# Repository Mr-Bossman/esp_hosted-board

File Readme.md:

# Test board for esp-hosted-ng

## Esp-hosted-ng is a SDIO/SPI WIFI/BT module for hosts runing Linux

To test ESP-Hosted-ng I designed this board to plug into and SD-card slot for easy testing.

The mothod I used before has some major signal integrity loss due to the jumper wires I used.

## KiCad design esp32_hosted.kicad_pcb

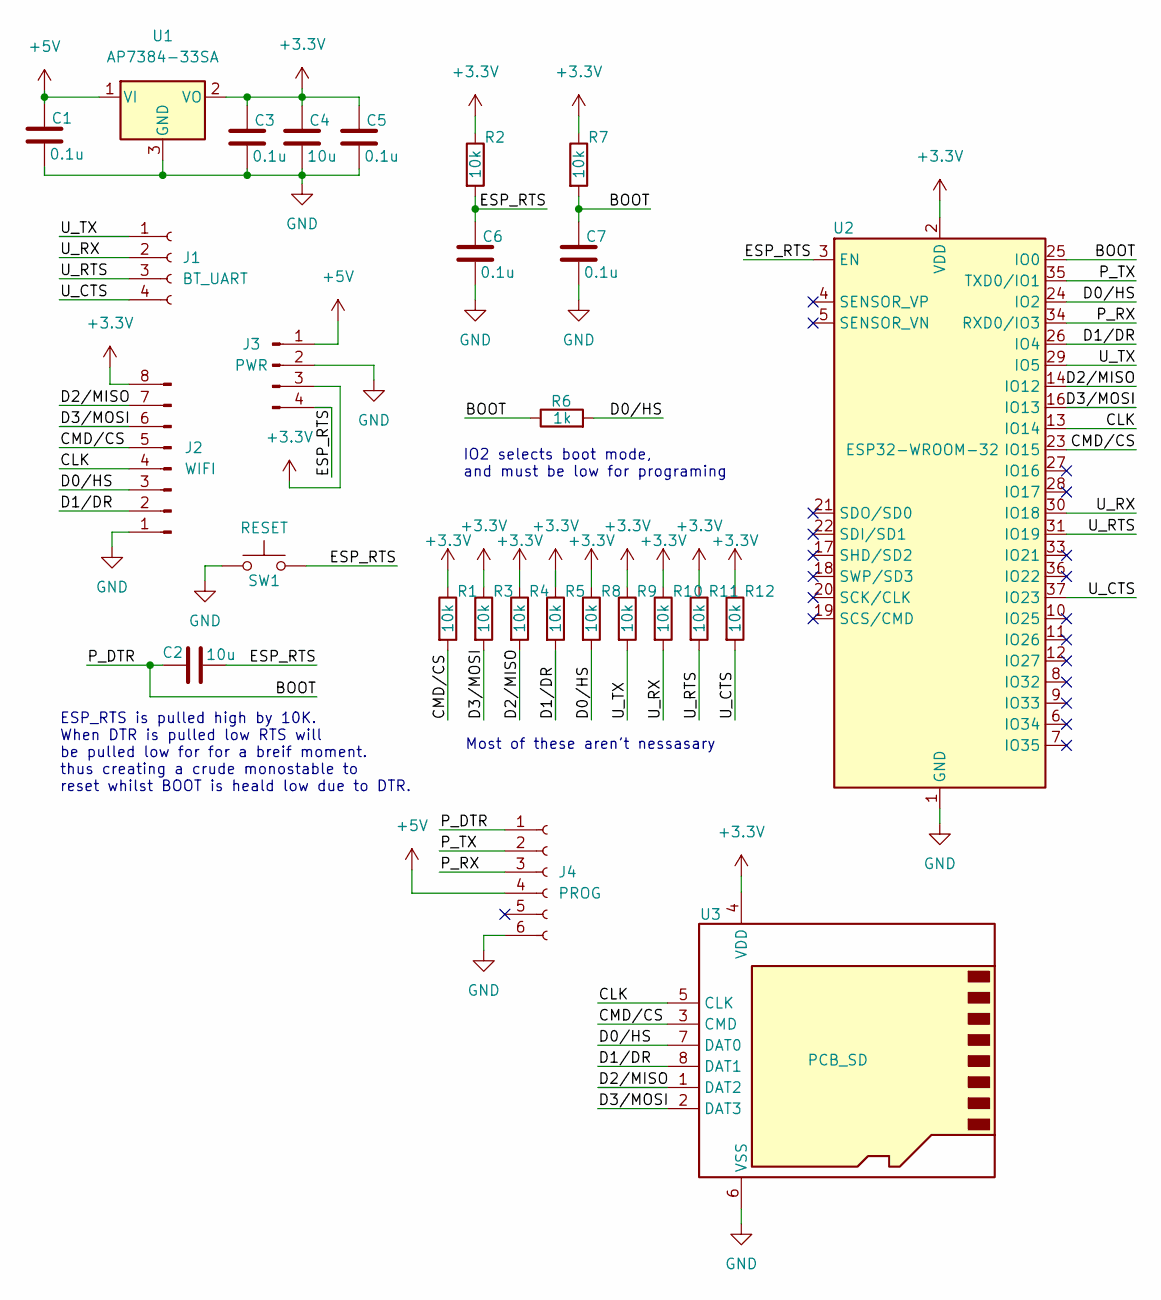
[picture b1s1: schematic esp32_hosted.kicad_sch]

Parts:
C1, C3, C5, C6, C7: 0.1u; C_0603_1608Metric_Pad1.08x0.95mm_HandSolder
C2, C4: 10u; C_0603_1608Metric_Pad1.08x0.95mm_HandSolder
J1: BT_UART; PinSocket_1x04_P2.54mm_Vertical
J2: WIFI; PinSocket_1x08_P2.54mm_Vertical
J3: PWR; PinSocket_1x04_P2.54mm_Vertical
J4: PROG; PinHeader_1x06_P2.54mm_Vertical
R1, R2, R3, R4, R5, R7, R8, R9, R10, R11, R12: 10k; C_0603_1608Metric_Pad1.08x0.95mm_HandSolder
R6: 1k; C_0603_1608Metric_Pad1.08x0.95mm_HandSolder
SW1: RESET; SW_PUSH_6mm
U1: AP7384-33SA; SOT-23
U2: ESP32-WROOM-32
U3: PCB_SD; PCB-SD

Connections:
+3.3V: C3.1, C4.1, C5.1, J2.8, J3.3, R1.1, R2.1, R3.1, R4.1, R5.1, R7.1, R8.1, R9.1, R10.1, R11.1, R12.1, U1.2 (VO), U2.2 (VDD), U3.4 (VDD)
+5V: C1.1, J3.1, J4.4, U1.1 (VI)
/BOOT: C2.1, C7.1, J4.1, R6.1, R7.2, U2.25 (IO0)
/CLK: J2.4, U2.13 (IO14), U3.5 (CLK)
/CMD/CS: J2.5, R1.2, U2.23 (IO15), U3.3 (CMD)
/D0/HS: J2.3, R6.2, R8.2, U2.24 (IO2), U3.7 (DAT0)
/D1/DR: J2.2, R5.2, U2.26 (IO4), U3.8 (DAT1)
/D2/MISO: J2.7, R4.2, U2.14 (IO12), U3.1 (DAT2)
/D3/MOSI: J2.6, R3.2, U2.16 (IO13), U3.2 (DAT3)
/ESP_RTS: C2.2, C6.1, J3.4, R2.2, SW1.2, U2.3 (EN)
/P_RX: J4.3, U2.34 (RXD0/IO3)
/P_TX: J4.2, U2.35 (TXD0/IO1)
/U_CTS: J1.4, R12.2, U2.37 (IO23)
/U_RTS: J1.3, R11.2, U2.31 (IO19)
/U_RX: J1.2, R10.2, U2.30 (IO18)
/U_TX: J1.1, R9.2, U2.29 (IO5)
GND: C1.2, C3.2, C4.2, C5.2, C6.2, C7.2, J2.1, J3.2, J4.6, SW1.1, U1.3 (GND), U2.1 (GND), U2.15 (GND), U2.38 (GND), U2.39 (GND), U3.6 (VSS)

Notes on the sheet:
IO2 selects boot mode, and must be low for programing
ESP_RTS is pulled high by 10K. When DTR is pulled low RTS will be pulled low for for a breif moment. thus creating a crude monostable to reset whilst BOOT is heald low due to DTR.
Most of these aren't nessasary

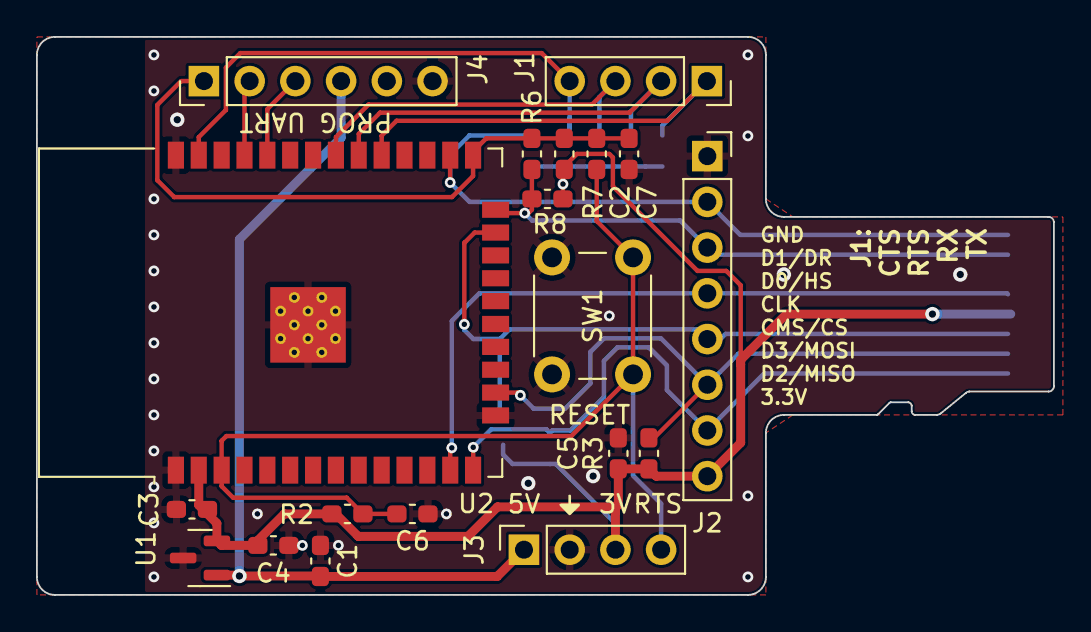
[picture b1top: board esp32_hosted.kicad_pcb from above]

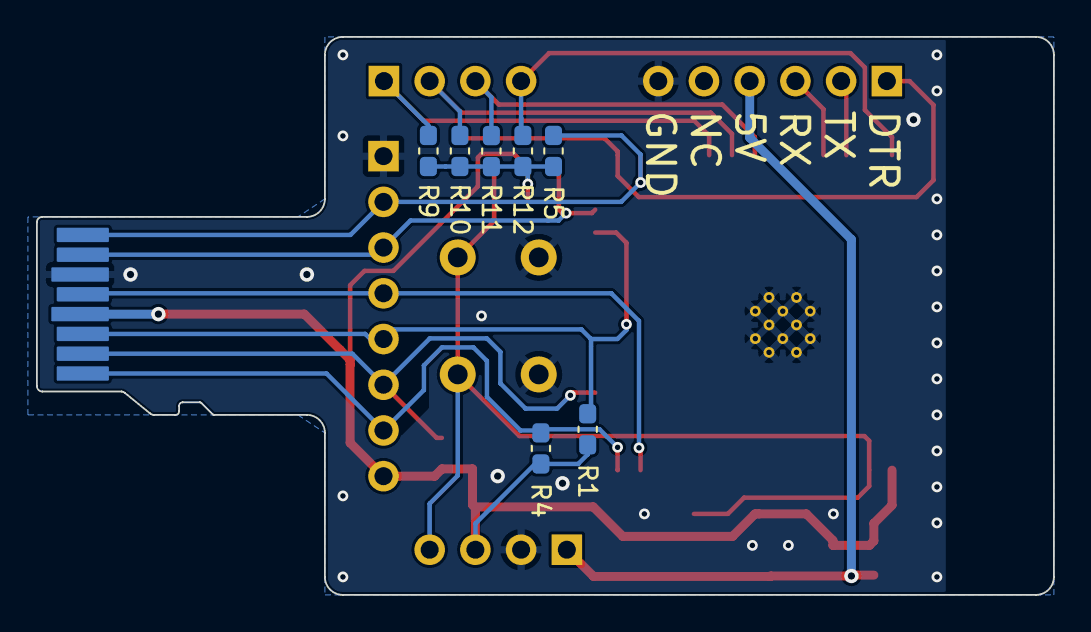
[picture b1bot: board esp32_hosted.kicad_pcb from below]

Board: 2 copper layers, 56.5 x 31.0 mm, 27 parts (7 on the bottom side), 17 nets.

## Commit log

2023-01-02 add images and readme
2023-01-02 forgot to breakout the reset pin
